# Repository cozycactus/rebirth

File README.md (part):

# ReBirth — RP2040 Pattern Sequencer

64-track, 16-step hardware sequencer inspired by [ReBirth RB-338](https://en.wikipedia.org/wiki/ReBirth_RB-338).
Built for the Raspberry Pi Pico (RP2040) — make full tracks without a computer using external synths and drum machines.

## Features

- **64 tracks × 16 steps** — SYNTH and DRUM on T1–T64, KIT available on T1–T8. TRACK scrolls through eight-column pages. SCENE addresses all 64 tracks.
- **Kit track** — one track plays a whole TR-909 style drum machine over DIN MIDI:
  12 lanes per step (accent plus 11 voices), three velocity levels and flams
- **32 pattern locations** arranged like ReBirth: banks A-D, slots 1-8
- **Independent pattern selection per track** — each track can play or queue a different bank/slot
- **Per-track pattern length** — each track can loop at 1-16 sixteenth-note steps
- **Live pattern editing** — step, length, and track-setting edits update playback while running
- **Session view** — 8×8 pad grid (tracks × slots of the shown bank), SCENE column,
  MUTE row and a PLAY button; the 16 step buttons edit the focused clip
- **Launch quantization** — pad and scene launches and MUTE changes land on the
  next bar (default), beat, step, or at the end of the track's loop
- **Song mode** — chain up to 384 rows of patterns with repeat counts, loop or stop at end
- **Pattern queue** — schedule the next pattern during playback
- **Track mutes** — MUTE changes at the launch point and flashes white while it
  waits; hold one MUTE key and press others to change several tracks together
- **Panic combo** — hold both encoder buttons to stop playback, drop gates, and send MIDI all-notes-off
- **Grouped gate edges** — two-phase output; DAC and DIN MIDI transfers remain sequential
- **MIDI output** — DIN-5 UART only, avoiding USB MIDI host scheduling jitter
- **Note entry from a MIDI keyboard** — hold a step on the Pattern view and press
  a key on a keyboard at the DIN input: the step takes the key's note and velocity
- **Pads as a keyboard** — while a step of a SYNTH clip is held, the 64 pads are a
  four-octave piano and a pad press sets the step's note, with no MIDI keyboard
- **CV/Gate output** — 4 channels via MCP4822 DACs (1V/oct, 12-bit; default 0-2.048 V)
- **MIDI Song playback** — import a timed MIDI arrangement with up to 64 source tracks and assign its output channels and CV/Gate pairs. [Import and playback](sim/README.md#midi-song)
- **96 PPQN** internal timing, **24 PPQN** MIDI Clock, 20–300 BPM
- **External clock** — follows a MIDI Clock on the DIN input (CLOCK INT / EXT /
  AUTO) with Start, Stop, Continue and Song Position Pointer; the OLED shows the
  measured tempo as `EXT 145.0`
- **Swing value** per pattern (playback timing pending)
- **Step flags** — accent, slide, tie (synth and drum tracks)

## Architecture

Dual-core split for low-jitter timing:

| Core | Role |
|------|------|
| **Core 1** | Sequencer engine — timer IRQ at 96 PPQN, step triggers, MIDI TX, CV/Gate |
| **Core 0** | UI — OLED display, encoders, buttons, pattern editing |

Shared writes and playback snapshots are protected by spinlocks. The sequencer ISR uses a two-phase commit:
1. **Collect** — buffer MIDI messages, stage CV/gate changes
2. **Commit** — simultaneous GPIO writes for gates, then queue MIDI buffer

DIN MIDI bytes are queued into a UART TX ring buffer and drained by UART0's TX interrupt, one byte per interrupt, so the sequencer timer ISR does not wait for MIDI serial transmission. MIDI Clock and Start/Continue/Stop go out at the next message boundary, ahead of queued note bytes.

## Hardware

| Function | GPIOs | Notes |
|----------|-------|-------|
| MIDI TX/RX | 0, 1 | UART0 @ 31250 baud; RX (J402, opto) takes a keyboard, see Live Controls |
| OLED (SSD1309) | 2–6 | SPI0, 128×64 |
| DAC (2× MCP4822) | 10–13 | SPI1, 4 CV channels |
| Gate outputs | 14–17 | 3.3V logic (4 channels) |
| Jitter probe | 7 | High while sequencer timer ISR runs |
| Encoders | 18–22, 26 | 2× rotary + push |
| I²C0 bus | 8, 9 | 400 kHz; external 2.2–4.7 kΩ pull-ups to 3.3 V (internal pulls are off) |
| I²C devices | on 8, 9 | MCP23017 0x20 step buttons 1-7 and 9-15, MCP23017 0x24 step buttons 8 and 16, MCP23017 0x21 step LEDs, MCP23017 0x22 + 0x23 panel key matrix scanner (pads, SCENE, MUTE) |
| Tempo LED | 25 | Pico on-board LED |
| RGB LED data | 27 | 82× SK6812MINI-E via PIO, buffered to 5 V |
| PLAY button | 28 | Momentary switch to GND, internal pull-up |

## Build

Requires [Raspberry Pi Pico SDK](https://github.com/raspberrypi/pico-sdk).

```bash
export PICO_SDK_PATH=/path/to/pico-sdk

mkdir build && cd build
cmake ..
make -j$(nproc)
```

Flash the resulting `.uf2` file by holding BOOTSEL and dragging to the Pico's USB drive.

The same firmware builds for a Pico 2 module (RP2350, Arm cores) with Pico SDK 2.2.0
installed in `~/.pico-sdk/sdk/2.2.0`:

```bash
cmake --preset pico2-release
cmake --build --preset pico2-release
```

The image is `build/pico2-release/rebirth_pico2.uf2`. The pins and the save addresses in
flash are those of the Pico. When exporting a song, choose **Pico 2 · RP2350** under
**Плата для UF2** in the [MIDI Song importer](sim/README.md#midi-song). The Pico 2 build
has not run on a board yet: see [HARDWARE_STATUS.md](HARDWARE_STATUS.md#needs-bench-verification).

The Rev B board ([hardware/rev-b](hardware/rev-b/README.md): RP2354B or RP2350B, four MIDI OUT,
microSD, every connector on the rear panel) has two presets, `revb-rp2354b` (2 MiB flash in the
package) and `revb-rp2350b` (external 16 MiB flash). Both set the DAC gain to 2x; the image is
named after the board, e.g. `build/revb-rp2354b/rebirth_revb_rp2354b.uf2`. No Rev B board has been
built yet.

The default DAC gain is 1x. For a board designed for 0-4.096 V CV, configure with
`-DREBIRTH_CV_DAC_GAIN=2`; the DAC supply and logic interface must support it.
See [ARCHITECTURE.md](ARCHITECTURE.md#cv-circuit) before choosing the hardware.

## Tests

Host-side unit tests (no hardware needed):

```bash
cd test
mkdir build && cd build
cmake ..
make -j$(nproc)

ctest --output-on-failure
```

Sixteen CTest targets (fifteen test sources; `test_sync` is built twice, once per DAC
gain) cover pattern/song data (`test_pattern`, `test_song`), the kit lane
helpers and settings (`test_kit`), the MIDI input parser (`test_midi_in`), MIDI/gate output at
both DAC gains (`test_sync`, `test_sync_gain2`), the real timer/transport code
(`test_playback`), following an external clock (`test_clock`), flash storage (`test_storage`), the Session view
(`test_session`), the LED frame builder (`test_led_frame`), the MCP23017 key
matrix scan driver (`test_key_scan`), the panel input on that scanner
(`test_panel_input`), the MCP23017 button/LED expanders and encoder
buttons (`test_expanders`), encoder clicks and their acceleration
(`test_encoder`) and UI/OLED rendering (`test_ui`). Launch
quantization runs in `sequencer.c` and is tested in `test_playback`.
Unix builds also exercise concurrent Stop/Panic during a pending gate commit.

## Live Controls

The Session view is home. The grid shows one bank (A-D) of 8 slots per track:
column = track, row = slot. Turning TRACK past an eight-track boundary displays
the next page. The OLED shows its track range. The **focus** is one cell (track, slot); the step
buttons edit it.

- **Pad:** launches that slot on the track at the next launch point and moves
  the focus there. While stopped the selection is immediate. Pressing a queued
  pad cancels the queue; pressing the playing pad changes nothing except that
  it cancels a pending queue to another slot of that track. An empty slot
  launches too, which silences the track.
- **Copy a clip:** hold a pad for half a second, then press another pad of the
  same track. The first pad's clip (steps, kit steps and length, not the
  track's routing or mute) is written over the second pad's, and the OLED
  shows `COPY A1>A3`. The second press does not launch or queue anything, so
  a clip that is playing or queued stays so and plays the copy. In the
  Session view the focus moves to the copy. The first pad stands for the
  clip it had when it was pressed, so changing the bank during the hold
  copies into another bank. Two pads pressed less than half a second apart are
  two launches, and a hold that the panel may have lost (after a panic, a
  save or load, or a panel error) is not trusted: press the source again.
  An existing clip in the target is overwritten and there is no undo.
- **SCENE:** launches the row on every track together; tracks already playing
  it keep playing. Pressed while any track is queued to that row, it cancels
  all queues.
- **MUTE:** toggles the track's mute at the next launch point, the one a pad
  launch would wait for (under TRACK LOOP the end of the track's loop, or the
  next bar in Song mode). While stopped, and under NEXT STEP, it acts at once.
  While the change waits, the MUTE key flashes white, one sixteenth white and
  one sixteenth its usual light. A second press before the launch point
  cancels the change; a press after it has landed is a new change. On a track
  silenced by a mute stored in an older save, MUTE makes the track audible and
  clears that stored mute in every slot; the track stays silent until the
  change lands, and stays muted if the change is cancelled.
- **Mute groups:** hold a MUTE key for half a second, then press other MUTE
  keys. The first key's own press is an ordinary MUTE press: it changes that
  key's track, or starts it waiting to change, as any MUTE press does. The
  other keys do not act: they are collected, and their keys are steady white.
  When the first key is let go, the collected tracks change together at the
  next launch point (at once while stopped or under NEXT STEP). Each other
  key changes its track to the opposite of the state the track had when the
  key joined. The first key goes with them if its own change was still
  waiting when the first other key joined: that change is taken back then,
  its key turns steady white, and it goes with the group to the target fixed
  at its press. If its change had already landed, acted at once or been
  cancelled by Stop, the first key stays out of the group. Pressing a
  collected key again takes it out; pressing a key whose change is waiting
  cancels that change and does not collect it. Under TRACK LOOP in Pattern
  mode each track changes at its own loop end, so they change together only
  when their loops end together. A MUTE key pressed less
  than half a second after the first is an ordinary press, so two fingers
  together are two presses. Stop keeps the group, and a release after Stop
  changes it at once. The stop the device makes itself when its MIDI output
  overflows does the same: the group is kept and its release changes it at
  once. A hold that the panel may have lost (after the panic combo of both
  encoder buttons, a save or load, or a panel error) is dropped and changes
  nothing, the first key's taken-back change included. Each MUTE key stands
  for the track in its column on the page shown when it is pressed, so a group
  can take tracks from several pages: hold the first key, turn TRACK to
  another page, press more. In the MIDI Song player the MUTE keys are the
  player's own and collect nothing.
- **PLAY:** starts and stops the transport; it is the only start/stop. Stop
  cancels pending queues and waiting MUTE changes.
- **Step buttons 1-16:** a short press toggles the step on release; a long
  press opens the step editor on that step without toggling it. Both act on
  the clip that was focused when the button went down, even if a pad or
  encoder 1 moves the focus before release; leaving the Session view drops
  the press. Steps beyond the clip's length do nothing.
- **Encoder 1 (TRACK):** turn to focus the previous/next track (on the slot it
  plays, or its queued one); press opens the pattern view on the focus; long
  press shows the next bank A → B → C → D → A.
- **Encoder 2 (VALUE):** turn for tempo; press cycles the launch quantization
  (1 BAR, 1 BEAT, NEXT STEP, TRACK LOOP; 1 BAR after power-up); long press opens
  the pattern selector on the focus.
- **Turning either encoder:** every screen counts whole clicks. A choice moves
  one per click however fast the turn: the focus, a list row, a kit lane, TYPE,
  OUTPUT, a kit step's value, the pattern slot and bank, the song cursor and a
  song entry's pattern. A number moves one per slow click and faster on a fast
  turn: clicks under 60 ms apart count 1 for the first four, then 4 each for
  three more, then 8 each. A pause of 60 ms or a turn back starts again at 1.
  Numbers are the tempo (0.1 BPM a step), a step's note and velocity, CHANNEL,
  GATE, a drum's NOTE, FLAM, the kit velocities and NOTE rows, and a song
  entry's repeats.
- Pads, SCENE, MUTE and PLAY work on every screen. Outside the Session view a
  pad launches without moving the focus.
- The step editor returns to the screen it was opened from. In the pattern
  view, encoder 1 long returns to the Session view; in the selector, encoder 2
  long does.
- The Pattern view of a SYNTH clip is a piano roll: time runs from top to
  bottom (step 1 at the top, four pixels a step) and pitch from left to right
  (four pixels a semitone, a window of 26 semitones that follows the clip's
  lowest and highest notes). A note is a 3x3 block, 4 wide with accent; a line
  under the block runs to the next note for a slide, and a single dot under it
  is a tie. A note outside the window is a bar at the left or right edge. Steps
  beyond the clip's length are a dotted line and show no notes, a row of dots
  after every fourth step marks the beats, and the step the track is playing is
  inverted. The four
  characters at the left show clip and track, length, the note at the window's
  left edge and the tempo; while a step is held they also show its number,
  note, velocity and flags (A accent, S slide, T tie), and a mark beside the
  step's rows. A DRUM clip keeps the step grid, and a kit its lanes.
- Pattern view step buttons on a SYNTH or DRUM track: a tap shorter than half
  a second toggles the step when the button is released. Hold one or more steps
  and turn encoder 1 for note or encoder 2 for velocity; encoder 1 short/long
  toggles accent/slide and encoder 2 long toggles tie on the held steps. The
  first edit of a held empty step creates it. A step held longer, or held while
  an encoder is turned or pressed, is not toggled on release. While a step is
  held the encoders do not change track, tempo or screen; pads, SCENE, MUTE and
  PLAY work as usual. On a kit track the step buttons edit the focused lane
  instead (see Editing a kit): a short press cycles it on release, a long press
  opens the kit step editor, and a held kit step takes no encoder, so TRACK
  still walks and VALUE still sets the tempo.
- A new SYNTH step starts at the note last entered on that track (C4 after
  power-up), not at C4: the last note is what a turn of encoder 1 on held steps
  or in the step editor left on the lowest step it changed. Steps that already
  have a note keep it, and DRUM and kit tracks do not use it. It is not saved.
  Holding empty steps and turning therefore moves them relative to it.
- **MIDI keyboard** on the DIN input (J402), any channel; notes only, no
  control change or pitch bend (a MIDI Clock there is the external clock, below). **Hold a step in the Pattern view and
  press a key:** the step is switched on if it was off and takes the key's
  note (SYNTH tracks) and velocity; two held steps take the same key, and a step
  that a key wrote to is not toggled on release. In the step editor the same
  works while the edited step's button is held (the step is not switched on or
  off). On a DRUM track the key sets the velocity only. **A key with no step
  held** sounds through the track being edited, on its MIDI channel (the
  focused track in the Session view, the configured one in track config), and
  becomes that track's last note, so the next steps switched on start there. A
  kit track passes the keys to its channel and nothing else. A key is released
  on the channel it started on, whatever the focus does meanwhile. At most half
  of the output queue is used by keys: a key pressed while it is that full is
  dropped, which cannot stop the sequencer. Keys are told apart by pitch, so
  two keys of one pitch on different keyboard channels count as one. A key lost
  at the UART (not counted) can give one wrong note; unplugging a keyboard
  with a key down leaves the note sounding until Panic. A keyboard's All Notes
  Off and All Sound Off release the notes it started, and so does a flash save
  or load.
- **Pads as a keyboard.** While a step of a SYNTH clip is held in the Pattern
  view (or the edited step's button in the step editor), the pads stop launching
  clips and are a keyboard: a pad press does what a key of the MIDI keyboard does
  (the held step is switched on if it was off and takes the note, the note is
  sounded on the track's channel), except that the velocity is always 100 and a
  step's own velocity is left alone. All eight columns are keys of the track being
  edited. Rows are paired from the bottom: in each pair the lower row is the white
  keys and the upper row the black keys, and the pairs are consecutive octaves.
  The window is fixed when the first step is held: the held step's octave (the
  track's last note for an empty step) is the second pair from the bottom, one
  octave below and two above, and it does not move until every step is let go.

  | Column | 1 | 2 | 3 | 4 | 5 | 6 | 7 | 8 |
  |---|---|---|---|---|---|---|---|---|
  | lower row (white) | C | D | E | F | G | A | B | C |
  | upper row (black) | - | C# | D# | - | F# | G# | A# | - |

  Lights: white keys are the track's colour at half level, black keys dim, the pads
  with no note are off, and every pad of the held step's note is white at full. In
  the Session view, on DRUM and kit cells and with no step held, the pads launch
  and copy as before. A pad released after its step still ends its note.
- Hold both encoder buttons for Panic: it stops playback and returns to the
  Session view. Release both before issuing another command; keys held through
  the panic or pressed while it is held do nothing afterwards.
- In the selector, buttons 1-8 mute on **short release**, at once whatever the
  launch quantization: a waiting change of that track is cancelled, and the
  track leaves a mute group. Holding opens track configuration without
  muting. Save/load (9/10) require stopped playback (and no start waiting for
  an external Clock); buttons, pads, MUTE and PLAY held through a save or load
  do nothing afterwards.
- **External clock.** In the selector, button 15 cycles the clock source:
  `CLOCK INT` (the device is the master, as at power-up), `CLOCK EXT` (it only
  follows a MIDI Clock on the DIN input) and `CLOCK AUTO` (it follows one when
  it is there, else runs on its own); the selector shows `CLK EXT` and button 15
  is lit when the source is not INT. It is not saved.
  - Each Clock received drives four of the 96 PPQN pulses: the first when it
    arrives, so every step starts on its Clock, the other three spaced by the
    measured tempo. Steps keep the master's timing, jitter included; a bunch of
    late Clocks is caught up quickly rather than played at once.
  - A Start from the master starts from the beginning on the first Clock after
    it; Stop stops; Continue goes on from where it stopped or from a Song
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
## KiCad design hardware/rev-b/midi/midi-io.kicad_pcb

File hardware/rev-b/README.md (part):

# ReBirth Rev B · RP2354B

Все внешние подключения Rev B находятся на задней стенке. Слева направо при взгляде со стороны штекеров идут **CV 1–4, GATE 1–4, microSD, USB Micro-B, MIDI IN и MIDI OUT A–D**. Габариты плат и крепёж соответствуют Rev A.

**Чертёж для примерки** можно распечатать на A4 при масштабе 100 %. Контрольный отрезок на листе равен 50 мм. DXF содержит наружный контур и 15 сквозных вырезов в миллиметрах. Начало координат находится в левом нижнем углу при взгляде снаружи. STEP содержит стенку в системе координат корпуса. PDF 1:1 собирается из [SVG](rear-panel.svg) командой в конце страницы. [DXF](rear-panel.dxf) · [STEP](rear-panel.step)

## Задняя стенка

Внешние размеры стенки между деревянными боковинами составляют **260 × 50 × 3 мм**. Внутренняя плоскость находится на Y = 132, внешняя на Y = 135. Верх основной платы лежит на высоте 9,6 мм от низа корпуса. Стенка имеет тот же наружный контур, что и в модели лотка Rev A. [Исходная модель корпуса](../panel/build_internals.py)

| Подключение | Принятый сквозной вырез | Посадка |
|---|---|---|
| 4 CV и 4 GATE | 8 × Ø7 мм | Втулка SJ1-3533NG имеет диаметр 6 мм, ось на 7 мм выше платы. Торец втулки выступает из стенки на 0,5 мм. [Чертёж Same Sky, стр. 2](https://www.sameskydevices.com/product/resource/sj1-353xng.pdf#page=2) |
| microSD | 16 × 10 мм, R3 | Окно центрировано по карте. От наружной поверхности край карты в защёлкнутом положении утоплен на 2,6 мм, для срабатывания её нужно нажать ещё на 0,8 мм. После отпускания край выступает на 1,4 мм. [Hirose DM3AT, чертёж](https://www.hirose.com/product/download/?distributor=chip1&lang=en&num=DM3AT-SF-PEJM5&type=2d) |
| USB Micro-B | 12 × 6,5 мм, R1,2 | Торец гнезда утоплен на 2,2 мм. Положение J301 сдвинуто на 1 мм в сторону MIDI IN для увеличения перемычки у microSD. [Amphenol 10104110](https://cdn.amphenol-cs.com/media/wysiwyg/files/drawing/10104110.pdf) |
| MIDI IN и 4 OUT | 5 × Ø18 мм | Ось SDS-50J расположена на 10 мм выше платы. От торца розетки до наружной поверхности 3,5 мм. Для штекера Same Sky SD-50 с корпусом Ø15,8 мм номинальный радиальный зазор в вырезе равен 1,1 мм. [Розетка, стр. 3](https://www.sameskydevices.com/product/resource/sds-j.pdf#page=3) · [Штекер, стр. 2](https://www.sameskydevices.com/product/resource/sd.pdf#page=2) |

Минимальная перемычка между вырезами составляет **2,425 мм** и находится между microSD и USB. Между ближайшими вырезами DIN остаётся 3,53 мм. Это размеры в CAD. Для физической примерки нужны плата на штатных стойках, карта и кабели с теми корпусами штекеров, которые будут использоваться одновременно.

В посадочных местах гнёзд SJ1‑3533NG и Amphenol 10104110 шелкография укорочена у края платы. Обе детали основаны на официальной библиотеке KiCad 10 и распространяются на условиях CC BY‑SA 4.0 с исключением для электронных проектов. [Лицензия библиотеки KiCad](KiCad-Libraries-LICENSE.md)

## Платы и верхняя панель

| Деталь | Что проверено в CAD |
|---|---|
| Основная плата | 244 × 57,5 мм. Контур с дугами, центры и сверловка всех семи креплений скопированы из Rev A. [Открыть плату](main-placement.kicad_pcb) |
| Панель | 248 × 251 мм. Сохранены семнадцать креплений и координаты имеющихся переключателей. Два новых тактовых переключателя REC и CYCLE расположены по сторонам от PLAY. [Открыть панель](panel-placement.kicad_pcb) |
| Пять DIN | Один вход и четыре независимых выхода на SDS-50J. Между монтажной зоной крайнего DIN и ближайшей зоной крепежа остаётся 0,43 мм. Шаг трёх соседних DIN составляет 21,53 мм. |
| Четыре CV и четыре Gate | Сквозные SJ1-3533NG шириной 8,2 мм. В KiCad их монтажная зона шириной 9,29 мм. Шаг осей 11,4 мм. |
| USB и microSD | Micro‑B Amphenol 10104110 и Hirose DM3AT-SF-PEJM5 размещены рядом на верхней стороне основной платы. От крайних контактных площадок обоих разъёмов до заднего края платы 0,5 мм. [Amphenol](https://cdn.amphenol-cs.com/media/wysiwyg/files/drawing/10104110.pdf) · [Hirose](https://www.hirose.com/en/product/p/CL0609-0031-0-00) |
| Экран | EastRising ER-TFT035IPS-6, без сенсора, ILI9488, 4-проводный SPI. В горизонтальном положении корпус со сложенным шлейфом 83 × 54,5 × 2,3 мм. Экран крепится под верхней крышкой. Между стеклом и ближайшей зоной крепления в проекции 1,25 мм. [Чертёж EastRising, стр. 5–6](https://www.buydisplay.com/download/manual/ER-TFT035IPS-6_Datasheet.pdf#page=6) |

В системе координат корпуса X направлен вправо для музыканта перед прибором, Y к задней стенке, Z вверх. Чтобы перенести точку из сборки на чертёж задней стенки, из 130 мм вычитают её X в корпусе. Высота Z сохраняется.

## Комплектации процессора и flash

Микроконтроллер в корпусе QFN‑80 устанавливается на основную плату. У RP2354B и RP2350B совпадают посадочное место, распиновка и набор из 48 GPIO. В KiCad переключатель варианта применяет комплектацию к ведомости и монтажному экспорту. PDF схемы показывает основной вариант. [Даташит Raspberry Pi](https://pip-assets.raspberrypi.com/categories/1214-rp2350/documents/RP-008373-DS-3-rp2350-datasheet.pdf) · [Проект KiCad](midi/midi-io.kicad_pro) · [Схема](midi/midi-io.kicad_sch), PDF собирается командой в конце страницы

| Вариант KiCad | U301 | Загрузочная flash | U303 · C302 · R310 |
|---|---|---|---|
| Основной (`Default`) | RP2354B | 2 МиБ в корпусе процессора | DNP |
| `External-16MiB` | RP2350B | W25Q128JVSIQ, 16 МиБ | Установить |

В обеих комплектациях R301 имеет статус DNP. Кнопка BOOTSEL замыкает QSPI_SS на землю через R306, 1 кОм. SWD доступен на внутреннем J303. Переключатель варианта меняет только список устанавливаемых деталей. Для сравнения аппаратное питание ядра 1,1 В, кварц 12 МГц, QSPI и USB сверены по 165 соединениям с проектом RP2350B Minimal R4/S1. Посадочные места QFN и двух деталей преобразователя взяты из него. [Аппаратное руководство Raspberry Pi, § 3.1](https://pip-assets.raspberrypi.com/categories/1214-rp2350/documents/RP-008280-DS-2-hardware-design-with-rp2350.pdf) · [Исходники Raspberry Pi](https://pip.raspberrypi.com/categories/1214-rp2350) · [Лицензия](Raspberry-Pi-LICENSE.txt) · [Лист USB и загрузки](midi/boot-usb.kicad_sch)

Питание логики 3,3 В формирует U302, TLV75533PDBVR, с керамическими конденсаторами по 4,7 мкФ на входе и выходе. У USB Micro‑B предусмотрен массив USBLC6‑2SC6, у процессора по 27 Ом в каждой линии данных. [TI TLV755P](https://www.ti.com/lit/ds/symlink/tlv755p.pdf) · [ST USBLC6‑2](https://www.st.com/resource/en/datasheet/usblc6-2.pdf)

Arm-сборка `revb-rp2354b` рассчитана на 2 МиБ flash, вариант `revb-rp2350b` на 16 МиБ. Код ограничен адресом `0x100B0000`. Выше идут 192 КиБ для текущего проекта, 1 МиБ для одной песни MIDI Song и 128 КиБ для сохранений старой восьмидорожечной прошивки. Линковщик проверяет обе границы. [Пресеты CMake](../../CMakePresets.json) · [Скрипт линковки](../../midi_song_flash.ld) · [Разметка сохранений](../../src/flash_storage.c)

## MIDI

Вход J402 соединён с UART0 через оптопару H11L1. У каждого выхода свой передатчик с 74LVC1G14, MMBT3904, резисторами токовой петли и ферритами. Проверка списка цепей сверяет номера выводов процессора, контакты 4 и 5 каждой DIN‑розетки и разделение четырёх TX. [Лист процессора](midi/processor.kicad_sch) · [Компоновка основной платы с цепями](midi/midi-io.kicad_pcb)

| DIN | GPIO | Вывод U301 | Назначение в Rev B |
|---|---|---|---|
| J402 IN | GP1 | 78 | UART0 RX через опторазвязку |
| J401 OUT A | GP0 | 77 | UART0 TX |
| J403 OUT B | GP23 | 23 | PIO TX |
| J404 OUT C | GP24 | 25 | PIO TX |
| J405 OUT D | GP29 | 37 | PIO TX |

Для модуля Pico 2 есть пресет `pico2-release` с одним DIN OUT. На модуле GP23, GP24 и GP29 заняты внутри, поэтому выходы B–D там недоступны. [Сборка для Pico 2](../../README.md#build) · [Распиновка Pico 2, § 5.2](https://datasheets.raspberrypi.com/pico/pico-2-datasheet.pdf#page=15)

## microSD

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
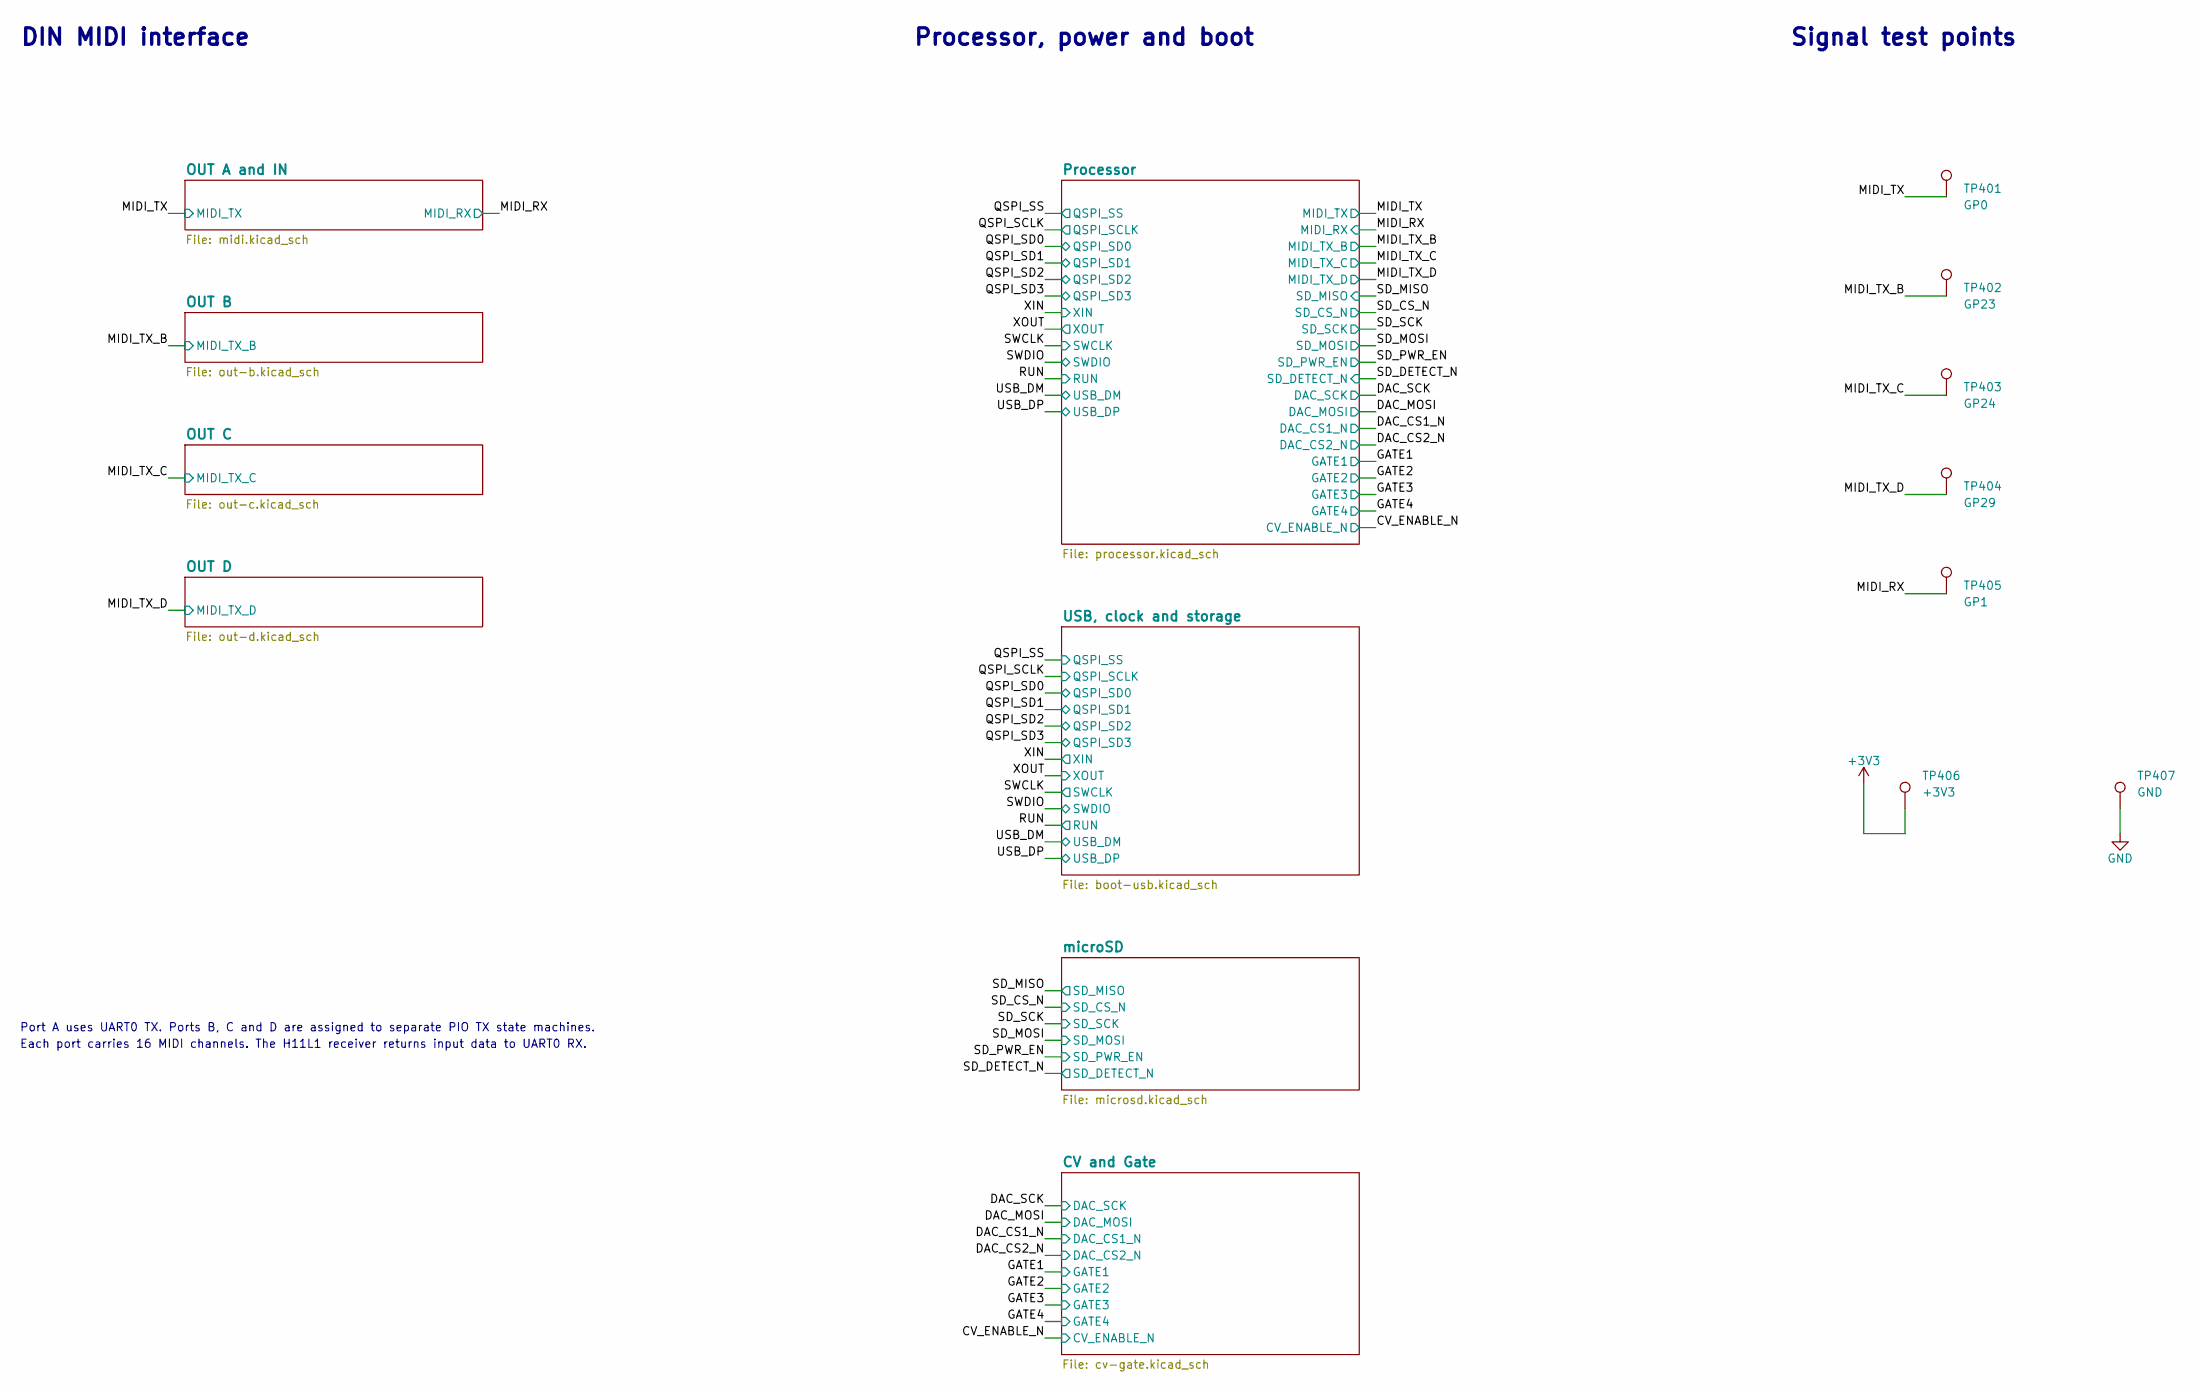
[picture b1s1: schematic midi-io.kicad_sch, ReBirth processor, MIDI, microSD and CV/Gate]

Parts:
TP401: GP0; TestPoint_Pad_D1.5mm
TP402: GP23; TestPoint_Pad_D1.5mm
TP403: GP24; TestPoint_Pad_D1.5mm
TP404: GP29; TestPoint_Pad_D1.5mm
TP405: GP1; TestPoint_Pad_D1.5mm
TP406: +3V3; TestPoint_Pad_D1.5mm
TP407: GND; TestPoint_Pad_D1.5mm

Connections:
+3V3: TP406.1; also elsewhere on the board
/MIDI_RX: TP405.1; also elsewhere on the board
/MIDI_TX: TP401.1; also elsewhere on the board
/MIDI_TX_B: TP402.1; also elsewhere on the board
/MIDI_TX_C: TP403.1; also elsewhere on the board
/MIDI_TX_D: TP404.1; also elsewhere on the board
GND: TP407.1; also elsewhere on the board

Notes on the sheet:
DIN MIDI interface
Processor, power and boot
Signal test points
Port A uses UART0 TX. Ports B, C and D are assigned to separate PIO TX state machines.
Each port carries 16 MIDI channels. The H11L1 receiver returns input data to UART0 RX.

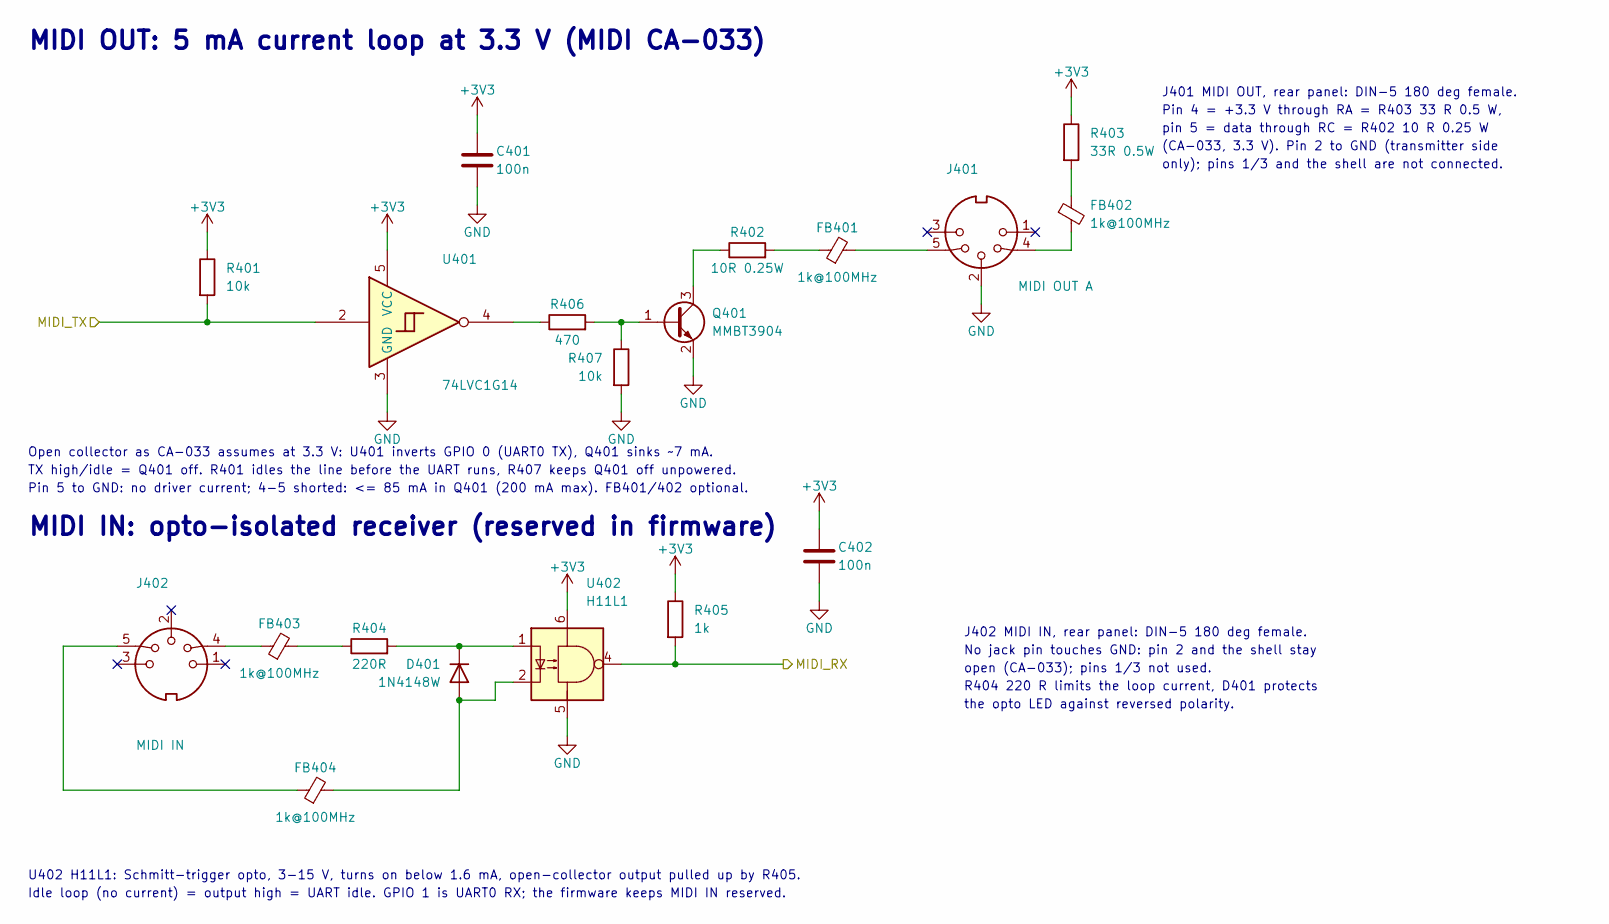
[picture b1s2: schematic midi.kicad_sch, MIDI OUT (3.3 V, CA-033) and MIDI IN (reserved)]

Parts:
C401, C402: 100n; C_0603_1608Metric
D401: 1N4148W; D_SOD-123
FB401, FB402, FB403, FB404: 1k@100MHz; L_0603_1608Metric
J401: MIDI OUT A; DIN-5_180deg_SameSky_SDS-50J_Horizontal
J402: MIDI IN; DIN-5_180deg_SameSky_SDS-50J_Horizontal
Q401: MMBT3904; SOT-23
R401, R407: 10k; R_0603_1608Metric
R402: 10R 0.25W; R_1206_3216Metric
R403: 33R 0.5W; R_1210_3225Metric
R404: 220R; R_0603_1608Metric
R405: 1k; R_0603_1608Metric
R406: 470; R_0603_1608Metric
U401: 74LVC1G14; SOT-23-5
U402: H11L1; DIP-6_W7.62mm

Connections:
+3V3: C401.1, C402.1, R401.1, R403.1, R405.1, U401.5 (VCC), U402.6; also elsewhere on the board
/MIDI_RX: R405.2, U402.4; also elsewhere on the board
/MIDI_TX: R401.2, U401.2; also elsewhere on the board
GND: C401.2, C402.2, J401.2, Q401.2 (E), R407.2, U401.3 (GND), U402.5; also elsewhere on the board
unnamed: D401.2 (A), FB404.2, U402.2
unnamed: D401.1 (K), R404.2, U402.1
unnamed: FB401.1, R402.2
unnamed: FB401.2, J401.5
unnamed: FB402.1, R403.2
unnamed: FB402.2, J401.4
unnamed: FB403.1, J402.4
unnamed: FB403.2, R404.1
unnamed: FB404.1, J402.5
unnamed: Q401.1 (B), R406.2, R407.1
unnamed: Q401.3 (C), R402.1
unnamed: R406.1, U401.4

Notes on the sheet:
MIDI OUT: 5 mA current loop at 3.3 V (MIDI CA-033)
J401 MIDI OUT, rear panel: DIN-5 180 deg female.
Pin 4 = +3.3 V through RA = R403 33 R 0.5 W,
pin 5 = data through RC = R402 10 R 0.25 W
(CA-033, 3.3 V). Pin 2 to GND (transmitter side
only); pins 1/3 and the shell are not connected.
Open collector as CA-033 assumes at 3.3 V: U401 inverts GPIO 0 (UART0 TX), Q401 sinks ~7 mA.
TX high/idle = Q401 off. R401 idles the line before the UART runs, R407 keeps Q401 off unpowered.
Pin 5 to GND: no driver current; 4-5 shorted: <= 85 mA in Q401 (200 mA max). FB401/402 optional.
MIDI IN: opto-isolated receiver (reserved in firmware)
J402 MIDI IN, rear panel: DIN-5 180 deg female.
No jack pin touches GND: pin 2 and the shell stay
open (CA-033); pins 1/3 not used.
R404 220 R limits the loop current, D401 protects
the opto LED against reversed polarity.
U402 H11L1: Schmitt-trigger opto, 3-15 V, turns on below 1.6 mA, open-collector output pulled up by R405.
Idle loop (no current) = output high = UART idle. GPIO 1 is UART0 RX; the firmware keeps MIDI IN reserved.

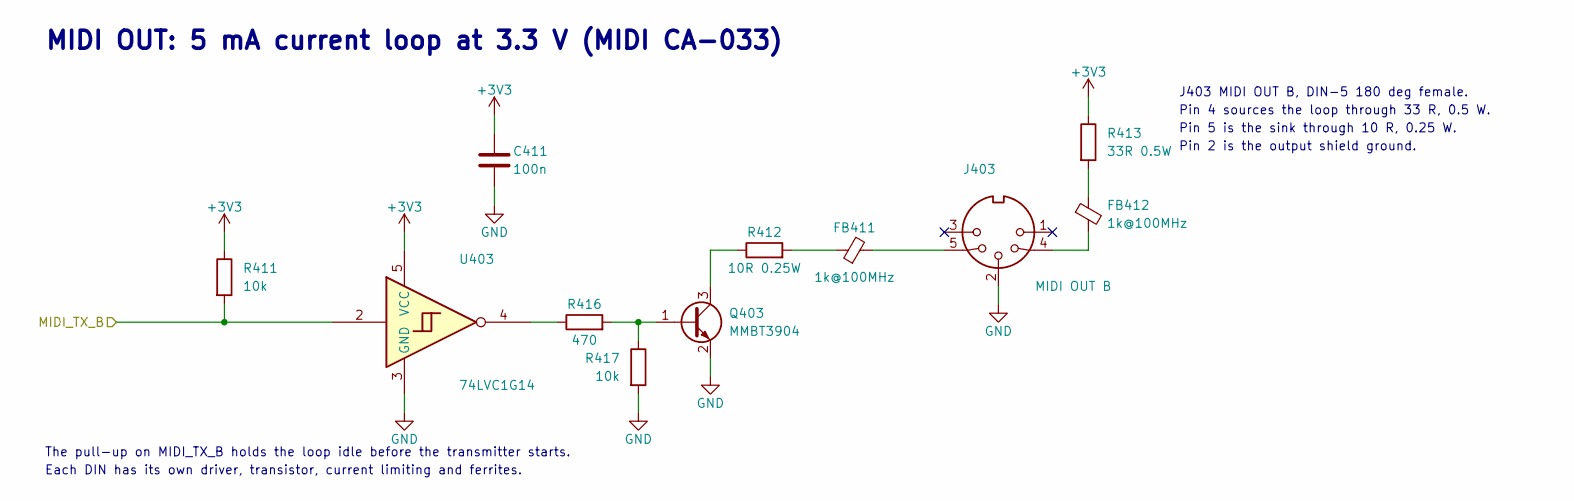
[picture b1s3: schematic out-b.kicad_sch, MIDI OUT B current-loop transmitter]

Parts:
C411: 100n; C_0603_1608Metric
FB411, FB412: 1k@100MHz; L_0603_1608Metric
J403: MIDI OUT B; DIN-5_180deg_SameSky_SDS-50J_Horizontal
Q403: MMBT3904; SOT-23
R411, R417: 10k; R_0603_1608Metric
R412: 10R 0.25W; R_1206_3216Metric
R413: 33R 0.5W; R_1210_3225Metric
R416: 470; R_0603_1608Metric
U403: 74LVC1G14; SOT-23-5

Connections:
+3V3: C411.1, R411.1, R413.1, U403.5 (VCC); also elsewhere on the board
/MIDI_TX_B: R411.2, U403.2; also elsewhere on the board
GND: C411.2, J403.2, Q403.2 (E), R417.2, U403.3 (GND); also elsewhere on the board
unnamed: FB411.1, R412.2
unnamed: FB411.2, J403.5
unnamed: FB412.1, R413.2
unnamed: FB412.2, J403.4
unnamed: Q403.1 (B), R416.2, R417.1
unnamed: Q403.3 (C), R412.1
unnamed: R416.1, U403.4

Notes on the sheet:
MIDI OUT: 5 mA current loop at 3.3 V (MIDI CA-033)
J403 MIDI OUT B, DIN-5 180 deg female.
Pin 4 sources the loop through 33 R, 0.5 W.
Pin 5 is the sink through 10 R, 0.25 W.
Pin 2 is the output shield ground.
The pull-up on MIDI_TX_B holds the loop idle before the transmitter starts.
Each DIN has its own driver, transistor, current limiting and ferrites.

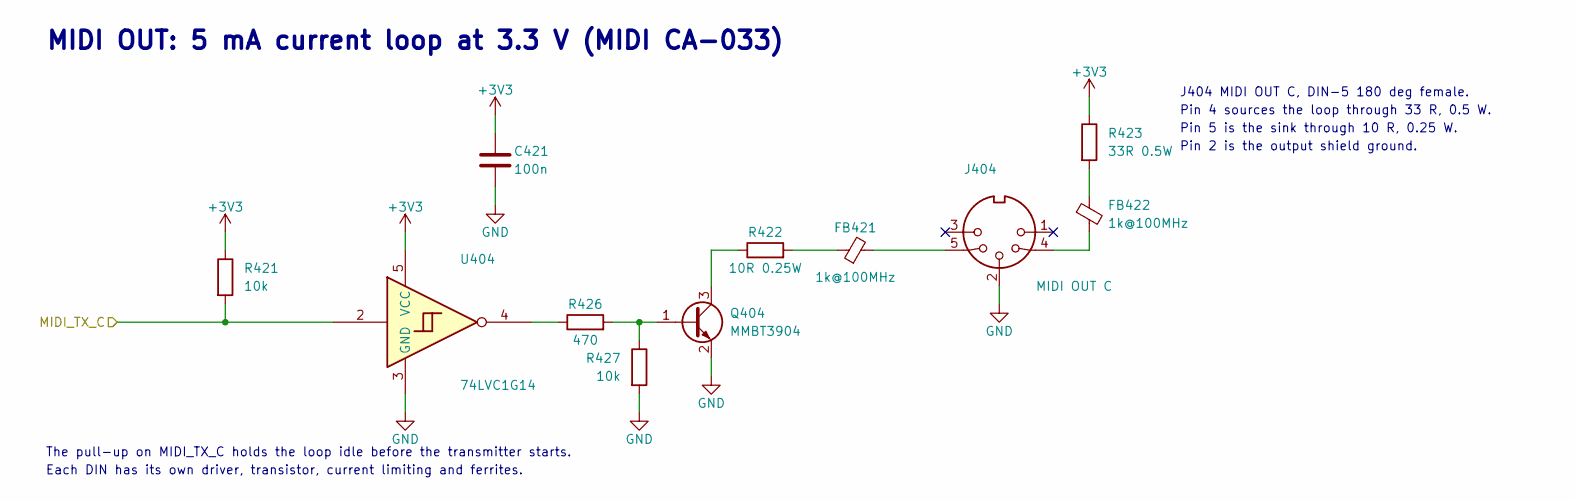
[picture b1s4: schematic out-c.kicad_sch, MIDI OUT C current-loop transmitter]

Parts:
C421: 100n; C_0603_1608Metric
FB421, FB422: 1k@100MHz; L_0603_1608Metric
J404: MIDI OUT C; DIN-5_180deg_SameSky_SDS-50J_Horizontal
Q404: MMBT3904; SOT-23
R421, R427: 10k; R_0603_1608Metric
R422: 10R 0.25W; R_1206_3216Metric
R423: 33R 0.5W; R_1210_3225Metric
R426: 470; R_0603_1608Metric
U404: 74LVC1G14; SOT-23-5

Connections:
+3V3: C421.1, R421.1, R423.1, U404.5 (VCC); also elsewhere on the board
/MIDI_TX_C: R421.2, U404.2; also elsewhere on the board
GND: C421.2, J404.2, Q404.2 (E), R427.2, U404.3 (GND); also elsewhere on the board
unnamed: FB421.1, R422.2
unnamed: FB421.2, J404.5
unnamed: FB422.1, R423.2
unnamed: FB422.2, J404.4
unnamed: Q404.1 (B), R426.2, R427.1
unnamed: Q404.3 (C), R422.1
unnamed: R426.1, U404.4

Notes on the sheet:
MIDI OUT: 5 mA current loop at 3.3 V (MIDI CA-033)
J404 MIDI OUT C, DIN-5 180 deg female.
Pin 4 sources the loop through 33 R, 0.5 W.
Pin 5 is the sink through 10 R, 0.25 W.
Pin 2 is the output shield ground.
The pull-up on MIDI_TX_C holds the loop idle before the transmitter starts.
Each DIN has its own driver, transistor, current limiting and ferrites.

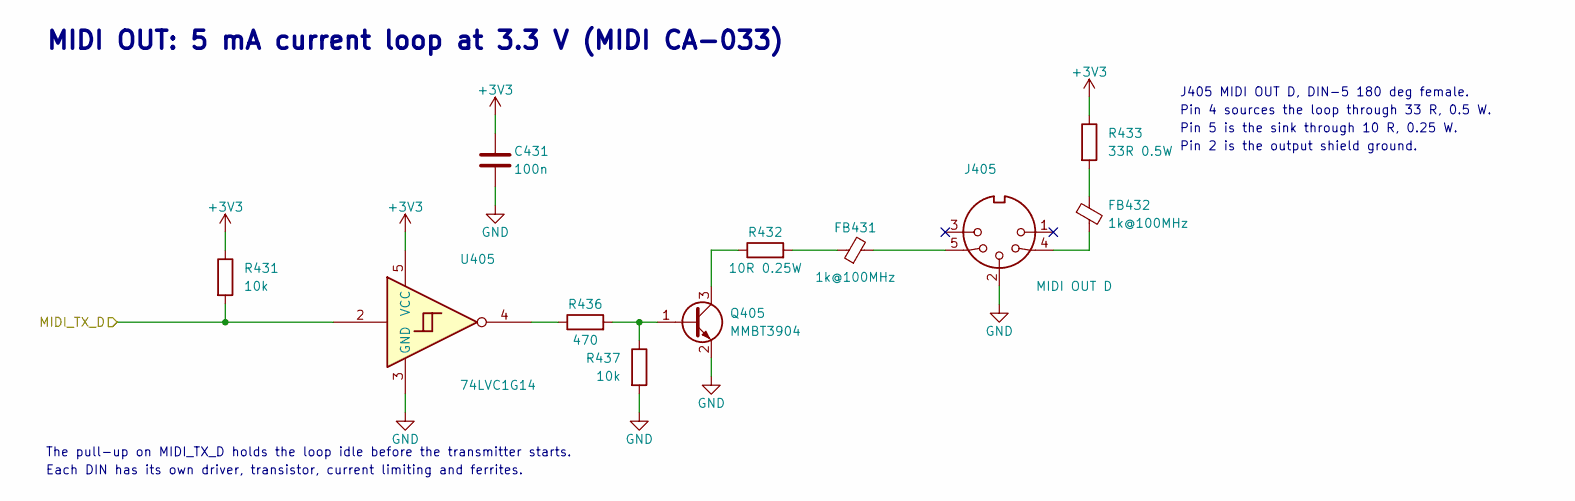
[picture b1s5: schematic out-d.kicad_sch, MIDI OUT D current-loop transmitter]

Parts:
C431: 100n; C_0603_1608Metric
FB431, FB432: 1k@100MHz; L_0603_1608Metric
J405: MIDI OUT D; DIN-5_180deg_SameSky_SDS-50J_Horizontal
Q405: MMBT3904; SOT-23
R431, R437: 10k; R_0603_1608Metric
R432: 10R 0.25W; R_1206_3216Metric
R433: 33R 0.5W; R_1210_3225Metric
R436: 470; R_0603_1608Metric
U405: 74LVC1G14; SOT-23-5

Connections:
+3V3: C431.1, R431.1, R433.1, U405.5 (VCC); also elsewhere on the board
/MIDI_TX_D: R431.2, U405.2; also elsewhere on the board
GND: C431.2, J405.2, Q405.2 (E), R437.2, U405.3 (GND); also elsewhere on the board
unnamed: FB431.1, R432.2
unnamed: FB431.2, J405.5
unnamed: FB432.1, R433.2
unnamed: FB432.2, J405.4
unnamed: Q405.1 (B), R436.2, R437.1
unnamed: Q405.3 (C), R432.1
unnamed: R436.1, U405.4

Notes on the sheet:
MIDI OUT: 5 mA current loop at 3.3 V (MIDI CA-033)
J405 MIDI OUT D, DIN-5 180 deg female.
Pin 4 sources the loop through 33 R, 0.5 W.
Pin 5 is the sink through 10 R, 0.25 W.
Pin 2 is the output shield ground.
The pull-up on MIDI_TX_D holds the loop idle before the transmitter starts.
Each DIN has its own driver, transistor, current limiting and ferrites.

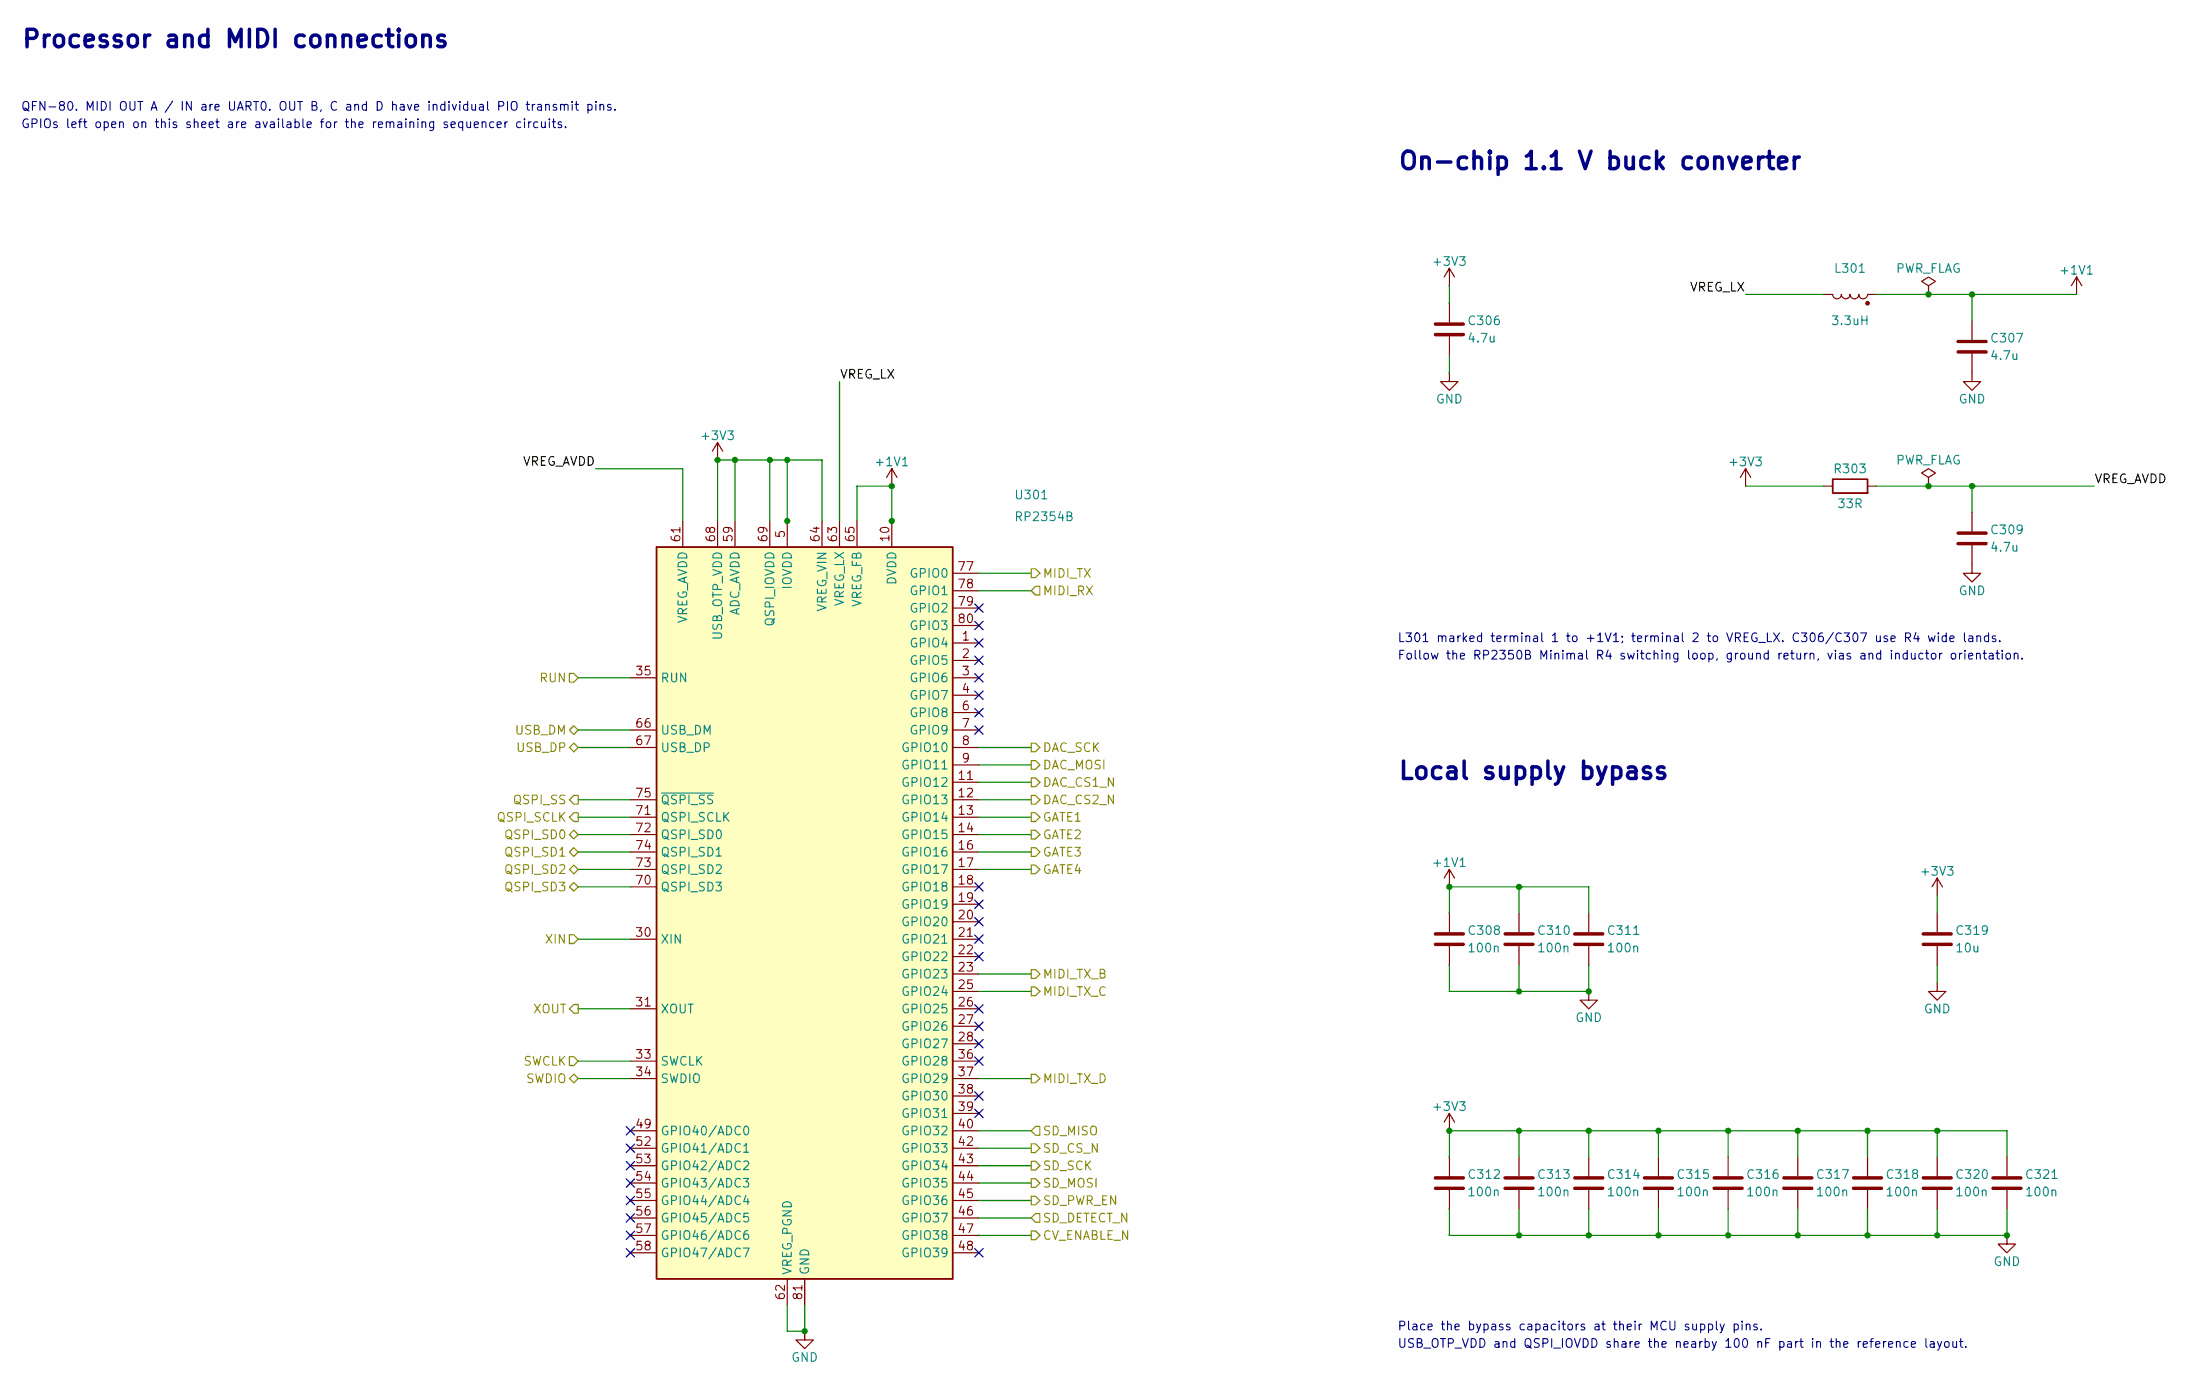
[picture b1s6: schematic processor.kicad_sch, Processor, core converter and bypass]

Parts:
C306, C307: 4.7u; C_0402_RP2350_VREG
C308, C310, C311, C312, C313, C314, C315, C316, C317, C318, C320, C321: 100n; C_0402_1005Metric
C309: 4.7u; C_0402_1005Metric
C319: 10u; C_0805_2012Metric
L301: 3.3uH; L_Abracon_AOTA-B201610S3R3-101-T; MPN AOTA-B201610S3R3-101-T
R303: 33R; R_0402_1005Metric
U301: RP2354B; RP2350B_QFN80_Minimal_R4; MPN RP2354B

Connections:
+1V1: C307.1, C308.1, C310.1, C311.1, L301.1, U301.10 (DVDD), U301.32 (DVDD), U301.51 (DVDD), U301.65 (VREG_FB)
+3V3: C306.1, C312.1, C313.1, C314.1, C315.1, C316.1, C317.1, C318.1, C319.1, C320.1, C321.1, R303.1, U301.5 (IOVDD), U301.15 (IOVDD), U301.24 (IOVDD), U301.29 (IOVDD), U301.41 (IOVDD), U301.50 (IOVDD), U301.59 (ADC_AVDD), U301.60 (IOVDD), U301.64 (VREG_VIN), U301.68 (USB_OTP_VDD), U301.69 (QSPI_IOVDD), U301.76 (IOVDD); also elsewhere on the board
/CV_ENABLE_N: U301.47 (GPIO38); also elsewhere on the board
/DAC_CS1_N: U301.11 (GPIO12); also elsewhere on the board
/DAC_CS2_N: U301.12 (GPIO13); also elsewhere on the board
/DAC_MOSI: U301.9 (GPIO11); also elsewhere on the board
/DAC_SCK: U301.8 (GPIO10); also elsewhere on the board
/GATE1: U301.13 (GPIO14); also elsewhere on the board
/GATE2: U301.14 (GPIO15); also elsewhere on the board
/GATE3: U301.16 (GPIO16); also elsewhere on the board
/GATE4: U301.17 (GPIO17); also elsewhere on the board
/MIDI_RX: U301.78 (GPIO1); also elsewhere on the board
/MIDI_TX: U301.77 (GPIO0); also elsewhere on the board
/MIDI_TX_B: U301.23 (GPIO23); also elsewhere on the board
/MIDI_TX_C: U301.25 (GPIO24); also elsewhere on the board
/MIDI_TX_D: U301.37 (GPIO29); also elsewhere on the board
/Processor/VREG_AVDD: C309.1, R303.2, U301.61 (VREG_AVDD)
/Processor/VREG_LX: L301.2, U301.63 (VREG_LX)
/QSPI_SCLK: U301.71 (QSPI_SCLK); also elsewhere on the board
/QSPI_SD0: U301.72 (QSPI_SD0); also elsewhere on the board
/QSPI_SD1: U301.74 (QSPI_SD1); also elsewhere on the board
/QSPI_SD2: U301.73 (QSPI_SD2); also elsewhere on the board
/QSPI_SD3: U301.70 (QSPI_SD3); also elsewhere on the board
/QSPI_SS: U301.75 (~QSPI_SS); also elsewhere on the board
/RUN: U301.35 (RUN); also elsewhere on the board
/SD_CS_N: U301.42 (GPIO33); also elsewhere on the board
/SD_DETECT_N: U301.46 (GPIO37); also elsewhere on the board
/SD_MISO: U301.40 (GPIO32); also elsewhere on the board
/SD_MOSI: U301.44 (GPIO35); also elsewhere on the board
/SD_PWR_EN: U301.45 (GPIO36); also elsewhere on the board
/SD_SCK: U301.43 (GPIO34); also elsewhere on the board
/SWCLK: U301.33 (SWCLK); also elsewhere on the board
/SWDIO: U301.34 (SWDIO); also elsewhere on the board
/USB_DM: U301.66 (USB_DM); also elsewhere on the board
/USB_DP: U301.67 (USB_DP); also elsewhere on the board
/XIN: U301.30 (XIN); also elsewhere on the board
/XOUT: U301.31 (XOUT); also elsewhere on the board
GND: C306.2, C307.2, C308.2, C309.2, C310.2, C311.2, C312.2, C313.2, C314.2, C315.2, C316.2, C317.2, C318.2, C319.2, C320.2, C321.2, U301.62 (VREG_PGND), U301.81 (GND); also elsewhere on the board

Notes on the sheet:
Processor and MIDI connections
QFN-80. MIDI OUT A / IN are UART0. OUT B, C and D have individual PIO transmit pins.
GPIOs left open on this sheet are available for the remaining sequencer circuits.
On-chip 1.1 V buck converter
L301 marked terminal 1 to +1V1; terminal 2 to VREG_LX. C306/C307 use R4 wide lands.
Follow the RP2350B Minimal R4 switching loop, ground return, vias and inductor orientation.
Local supply bypass
Place the bypass capacitors at their MCU supply pins.
USB_OTP_VDD and QSPI_IOVDD share the nearby 100 nF part in the reference layout.

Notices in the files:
README.md:
GNU General Public License v3.0 — see [LICENSE](LICENSE).
Behavior of the original ReBirth RB-338 is taken from
[OpenRB-338](https://github.com/pingw33n/openrb-338) (also GPL-3.0).
parts and their libraries:
USB Micro-B, horizontal, https://cdn.amphenol-icc.com/media/wysiwyg/files/drawing/10104110.pdf. ReBirth Rev B rear edge silkscreen, based on the KiCad Library (CC-BY-SA-4.0).
